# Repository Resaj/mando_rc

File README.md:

# Mando RC
Mando radiocontrol con bluetooth.

Este mando fue diseñado en un principio para el robot de sumo teledirigido, [Kassius](https://github.com/Resaj/rc-sumo-kassius), pero puede programarse para otro tipo de robots y aplicaciones.

El microcontrolador empleado es el LPC2138, soldado sobre una placa comercial. Esto da la posibilidad de poder cambiarlo y sustituirlo por otro microcontrolador.

Está compuesto por dos joystick, dos pulsadores frontales, dos potenciómetros y varios leds de señalización. Con una batería lipo 1S y conexión para bluetooth y un módulo RF-nano. Se programa con un FTDI externo a través del conector del bluetooth.

## Autor
[Rubén Espino San José](https://github.com/Resaj)

## License

Todos estos productos están liberados mediante [Creative Commons Attribution-ShareAlike 4.0 International License](http://creativecommons.org/licenses/by-sa/4.0/).  
_All these products are released under [Creative Commons Attribution-ShareAlike 4.0 International License](http://creativecommons.org/licenses/by-sa/4.0/)._

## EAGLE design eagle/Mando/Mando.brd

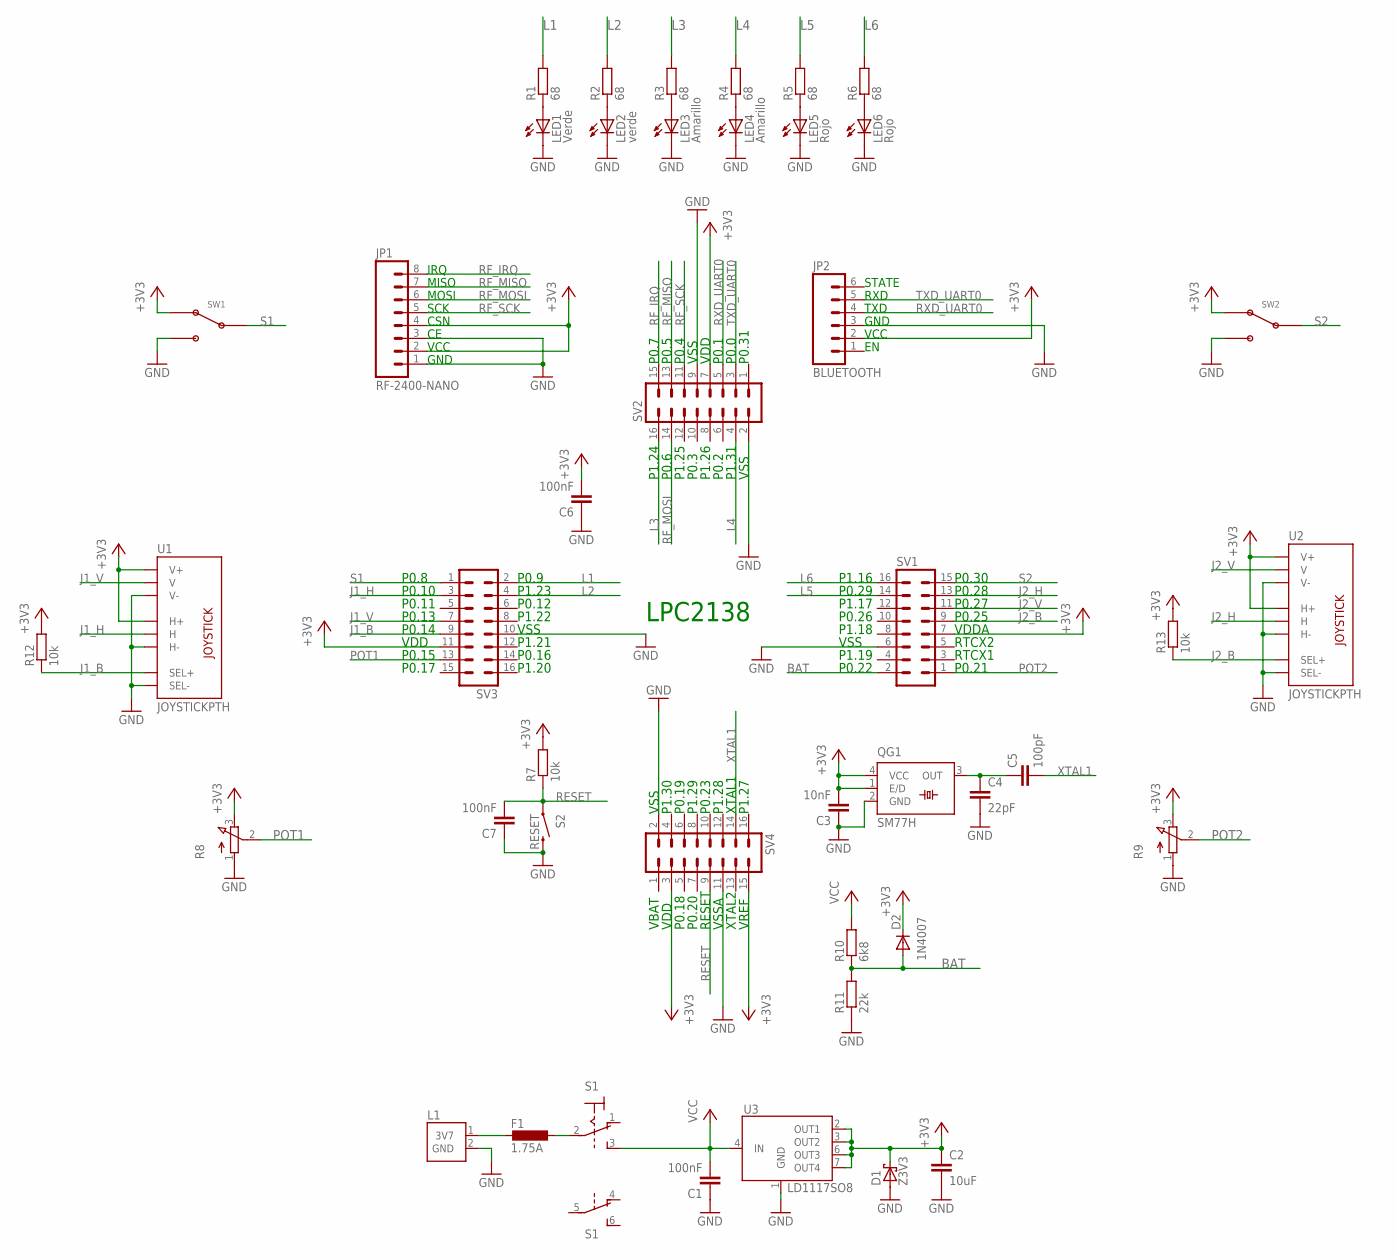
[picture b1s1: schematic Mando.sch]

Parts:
C1, C6, C7: 100nF; C0805
C2: 10uF; C1206
C3: 10nF; C0805
C4: 22pF; C0805
C5: 100pF; C0805
D1: Z3V3; DO35-7
D2: 1N4007; SOD106-R
F1: 1.75A; L1812
JP1: RF-2400-NANO; 1X08
JP2: BLUETOOTH; 1X06
L1: CONECTOR_LIPO_3.7V
LED1: Verde; LED3MM
LED2: verde; LED3MM
LED3, LED4: Amarillo; LED3MM
LED5, LED6: Rojo; LED3MM
QG1: SM77H
R1, R2, R3, R4, R5, R6: 68; M0805
R7, R12, R13: 10k; M0805
R8, R9: 3RP/1610N
R10: 6k8; M0805
R11: 22k; M0805
S1: SWITCH_2P2T_SL; SLIDE_SWITCH_2P2T
S2: RESET; TACTILE-PTH
SV1, SV2, SV3, SV4: MA08-2
SW1, SW2: SW_1382_R/A; SW_MX1382
U1, U2: JOYSTICKPTH; JOYSTICK
U3: LD1117SO8; SO8

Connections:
+3V3: C2.1, C3.2, C6.2, D1.C, D2.C, JP1.2, JP1.4, JP2.2, QG1.1 (E/D), QG1.4 (VCC), R7.2, R8.3 (E), R9.3 (E), R12.2, R13.2, SV1.7, SV2.7, SV3.11, SV4.3, SV4.15, SW1.N.C, SW2.N.C, U1.H1 (H+), U1.V1 (V+), U2.H1 (H+), U2.V1 (V+), U3.2 (OUT1), U3.3 (OUT2), U3.6 (OUT3), U3.7 (OUT4)
BAT: D2.A, R10.1, R11.2, SV1.2
GND: C1.1, C2.2, C3.1, C4.2, C6.1, C7.1, D1.A, JP1.1, JP1.3, JP2.3, L1.2 (GND), LED1.K (C), LED2.K (C), LED3.K (C), LED4.K (C), LED5.K (C), LED6.K (C), QG1.2 (GND), R8.1 (A), R9.1 (A), R11.1, S2.3 (2), SV1.6, SV2.2, SV2.9, SV3.10, SV4.2, SV4.11, SW1.N.O, SW2.N.O, U1.B2A (SEL-), U1.H3 (H-), U1.V3 (V-), U2.B2A (SEL-), U2.H3 (H-), U2.V3 (V-), U3.1 (GND)
J1_B: R12.1, SV3.9, U1.B1A (SEL+)
J1_H: SV3.3, U1.H2 (H)
J1_V: SV3.7, U1.V2 (V)
J2_B: R13.1, SV1.9, U2.B1A (SEL+)
J2_H: SV1.13, U2.H2 (H)
J2_V: SV1.11, U2.V2 (V)
L1: R1.2, SV3.2
L2: R2.2, SV3.4
L3: R3.2, SV2.16
L4: R4.2, SV2.4
L5: R5.2, SV1.14
L6: R6.2, SV1.16
unnamed: F1.2, L1.1 (3V7)
unnamed: F1.1, S1.2
unnamed: LED1.A, R1.1
unnamed: C4.1, C5.1, QG1.3 (OUT)
unnamed: LED2.A, R2.1
unnamed: LED3.A, R3.1
unnamed: LED4.A, R4.1
unnamed: LED5.A, R5.1
unnamed: LED6.A, R6.1
POT1: R8.2 (S), SV3.13
POT2: R9.2 (S), SV1.1
RESET: C7.2, R7.1, S2.1, SV4.9
RF_IRQ: JP1.8, SV2.15
RF_MISO: JP1.7, SV2.13
RF_MOSI: JP1.6, SV2.14
RF_SCK: JP1.5, SV2.11
RXD_UART0: JP2.4, SV2.5
S1: SV3.1, SW1.COM
S2: SV1.15, SW2.COM
TXD_UART0: JP2.5, SV2.3
VCC: C1.2, R10.2, S1.3 (S), U3.4 (IN)
XTAL1: C5.2, SV4.14

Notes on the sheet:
LPC2138
P0.21
P0.22
P0.25
P0.26
P0.27
P0.28
P0.29
P0.30
P0.31
P0.0
P1.31
P0.1
P0.2
P1.26
P0.3
P0.4
P0.5
P0.6
P0.7
P1.24
VBAT
VSS
VDD
P1.30
P0.18
P0.19
P0.20
P1.29
RESET
P0.23
VSSA
P1.28
XTAL2
XTAL1
VREF
P1.27
P1.20
P0.17
P0.8

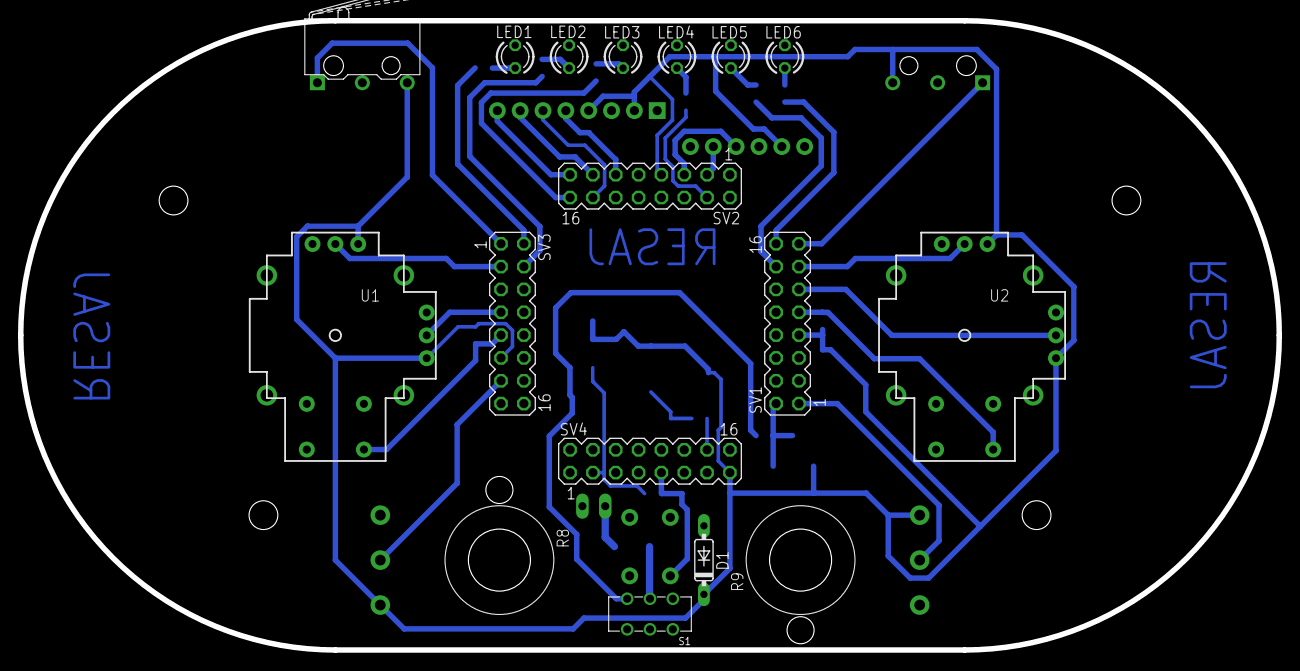
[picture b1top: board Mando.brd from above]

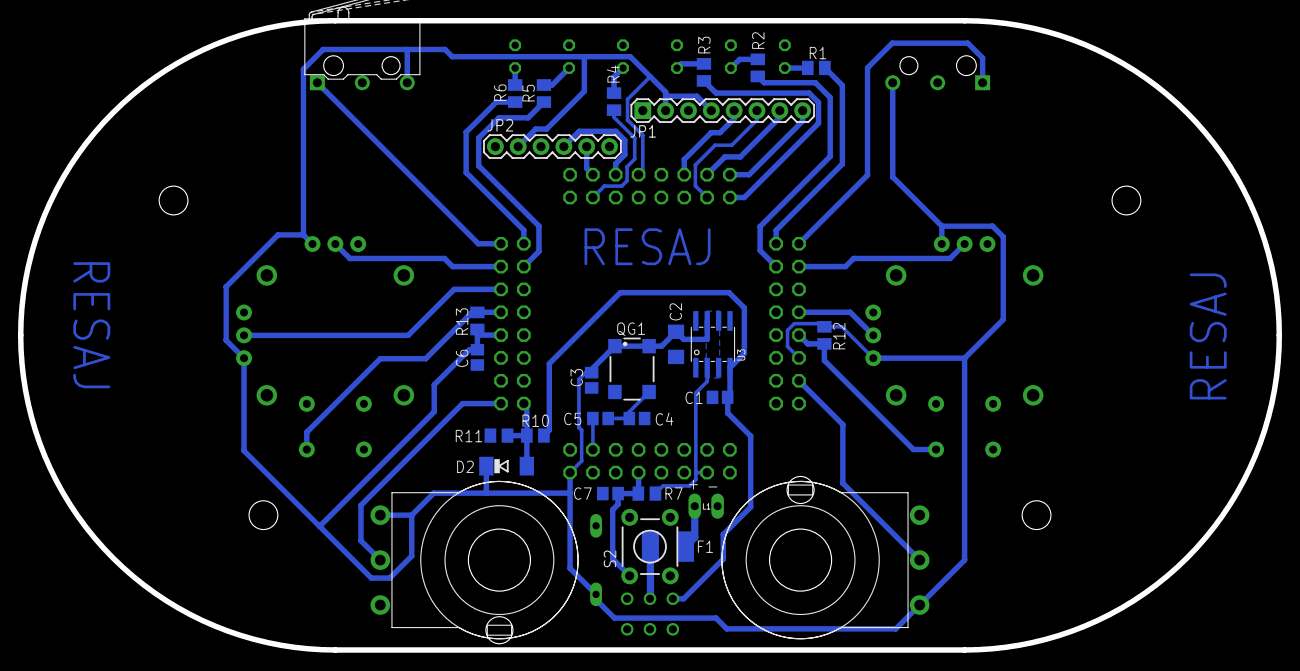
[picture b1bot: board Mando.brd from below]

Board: 2 copper layers, 140.0 x 70.0 mm, 44 parts (27 on the bottom side), 37 nets.

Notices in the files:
parts and their libraries:
SparkFun: Licensing: CC v3.0 Share-Alike You are welcome to use this library for commercial purposes.
